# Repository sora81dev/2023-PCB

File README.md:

# English version
## Abstract
Sora is all about the foundation created in 2023.  
## Contents of the data of each foundation
Data of the foundation (SCH&BRD)  
BOM & CPL  
## List of tested devices
None  
## Update
2023.02.26 15:32 : Create Repository  
2023.02.26 15:34 : Update README.md(Add to Lisence)  
2023.02.26 15:45 : Update README.md(Add to English Version)  
2023.02.26 20:30 : Upload Ball Sensor Board  
## Lisence
(CC)BY-NC-ND 4.0  
Applies to all works in this repository.  
# Japanese version
## Abstract
そらが2023に作成した基盤のすべてです。
## それぞれの基盤のデータの内容物
・基盤データ(SCH&BRD)  
・部品(BOM&CPL)  
## 動作確認済　一覧
なし
## Update
2023.02.26 15:32 : Create Repository  
2023.02.26 20:30 : Upload Ball Sensor Board  
2023.02.26 15:45 : Update README.md(Add to English Version)  
2023.02.26 20:30 : Upload Ball Sensor Board  
## Lisence
(CC)BY-NC-ND 4.0  
※このレポジトリー内のすべての制作物において適用いたします

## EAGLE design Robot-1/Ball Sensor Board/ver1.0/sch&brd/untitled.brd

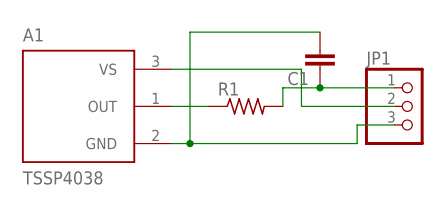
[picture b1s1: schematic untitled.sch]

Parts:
A1: TSSP4038; XDCR_TSSP4038
C1: C-EUC0402; C0402
JP1: PINHD-1X3/90; 1X03/90
R1: R-US_R0402; R0402

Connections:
unnamed: A1.1 (OUT), R1.1
unnamed: C1.1, JP1.1, R1.2
unnamed: A1.2 (GND), C1.2, JP1.3
unnamed: A1.3 (VS), JP1.2

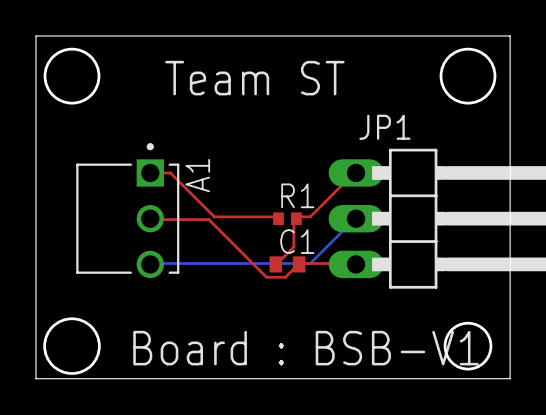
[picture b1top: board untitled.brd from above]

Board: 2 copper layers, 26.2 x 18.9 mm, 4 parts (0 on the bottom side), 4 nets.

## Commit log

2023-02-26 Upload BSB-V1.zip
2023-08-13 Ball Sensor Board File Upload
